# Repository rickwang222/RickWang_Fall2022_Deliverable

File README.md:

# RickWang_Fall2022_Deliverable

## 3D_Tag_Model Foler
3D_Holder.f3d file contains the 3D model of the 3D tag holder and can be opened and edited with Fusion 360
The PDF file contains the initial test result for 3 antennas and the materials used to build the 3D tag holder

## Arduino_Hat_RevB
This folder contains the original PCB file for the Arduino hat and can be open using Eagle, a BOM is also included in the form of Excel file

## PCB
This folder contains the Extension board PCB design as a Altium project. Download the entire folder and open the project will open both the PCB and schematic. The board is currently design to support 5 sets of antennas at the same time but can be expended by adding more ports. The input of the extension board is the output of the original Arduino hat. No softawre change needed for the extension board.

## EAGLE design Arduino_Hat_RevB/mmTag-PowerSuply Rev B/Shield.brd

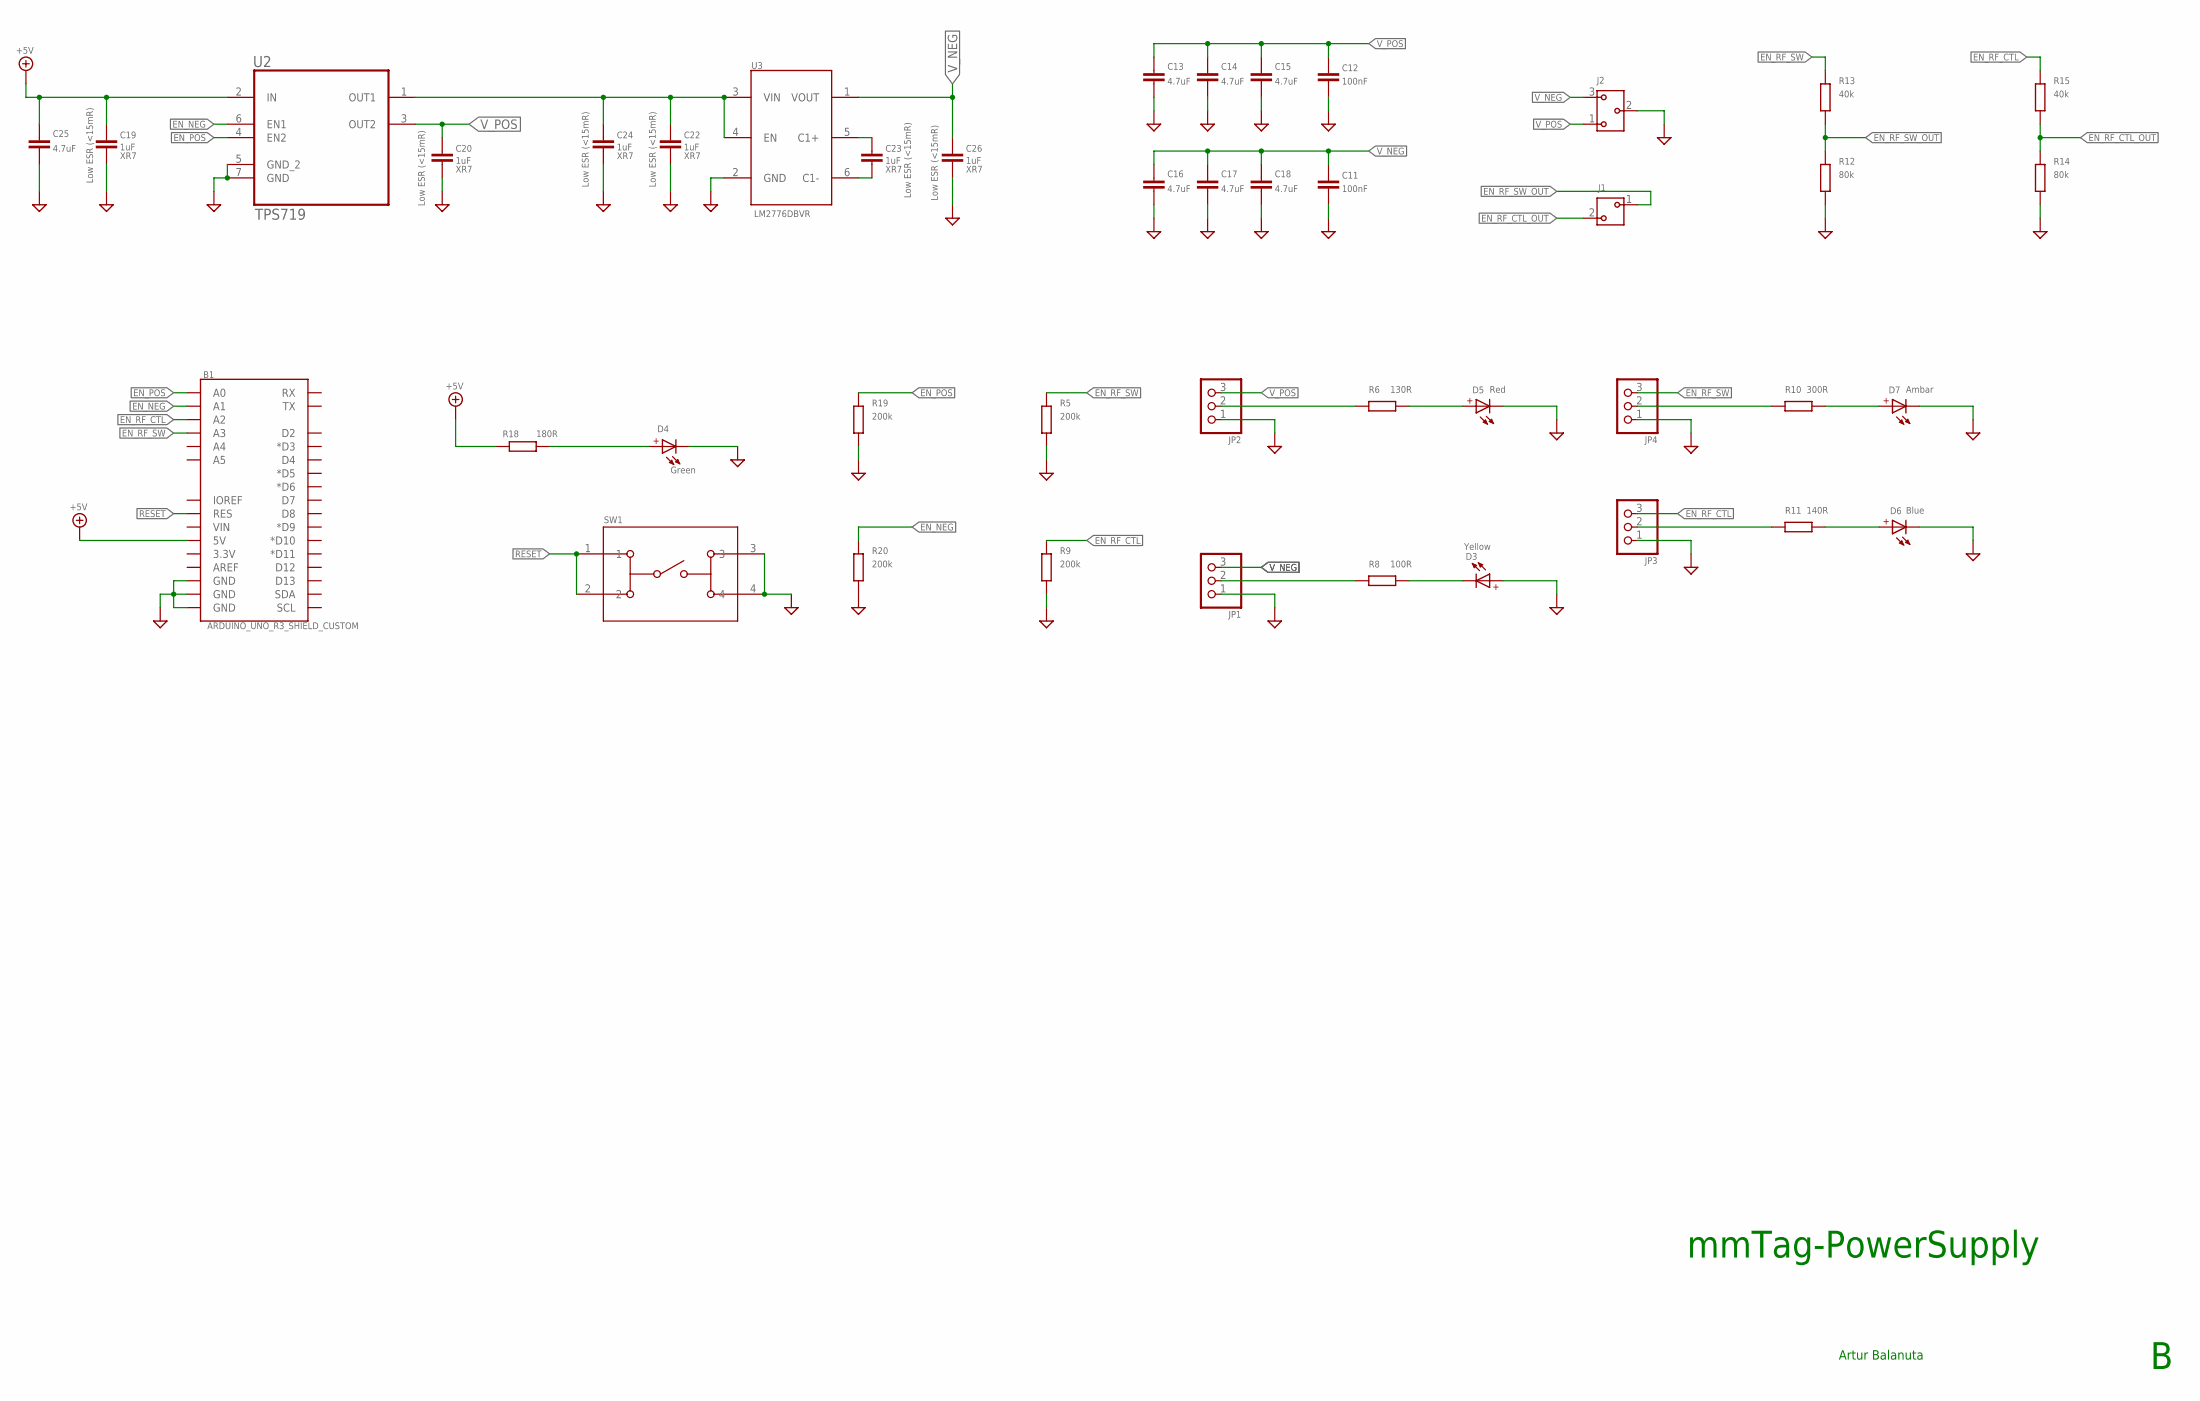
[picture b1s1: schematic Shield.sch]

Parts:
B1: ARDUINO_UNO_R3_SHIELD_CUSTOM; UNO_R3_SHIELD_NO_PROG
C11, C12: 100nF; C0603
C13, C14, C15, C16, C17, C18, C25: 4.7uF; C1206
C19, C20, C22, C23, C24, C26: 1uF; C0603
D3: WL-SMCW-150080YS75000; WL-SMCW_0805
D4: WL-SMCW-150080GS75000; WL-SMCW_0805
D5: WL-SMCW-150080RS75000; WL-SMCW_0805
D6: WL-SMCW-150080BS75000; WL-SMCW_0805
D7: WL-SMCW_150080AS75000; WL-SMCW_0805
J1: 691412320002
J2: 691412320003
JP1, JP2, JP3, JP4: PINHD-1X3; 1X03
R5, R9, R19, R20: 200k; R0603
R6: 130R; R0603
R8: 100R; R0603
R10: 300R; R0603
R11: 140R; R0603
R12, R14: 80k; R0603
R13, R15: 40k; R0603
R18: 180R; R0603
SW1: 1825910-6; SW4_1825910-B
U2: TPS719; SON6_5P200X200X80-7N
U3: LM2776DBVR; TEXAS_SOT23-6

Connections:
+5V: B1.5V, C19.1, C25.1, R18.1, U2.2 (IN)
EN_NEG: B1.A1, R20.1, U2.6 (EN1)
EN_POS: B1.A0, R19.1, U2.4 (EN2)
EN_RF_CTL: B1.A2, JP3.3, R9.1, R15.1
EN_RF_CTL_OUT: J1.2, R14.1, R15.2
EN_RF_SW: B1.A3, JP4.3, R5.1, R13.1
EN_RF_SW_OUT: J1.1, R12.1, R13.2
GND: B1.GND@0 (GND), B1.GND@1 (GND), B1.GND@2 (GND), C11.2, C12.2, C13.2, C14.2, C15.2, C16.2, C17.2, C18.2, C19.2, C20.2, C22.2, C24.2, C25.2, C26.2, D3.2 (+), D4.1 (-), D5.1 (-), D6.1 (-), D7.1 (-), J2.2, JP1.1, JP2.1, JP3.1, JP4.1, R5.2, R9.2, R12.2, R14.2, R19.2, R20.2, SW1.3, SW1.4, U2.5 (GND_2), U2.7 (GND), U3.2 (GND)
unnamed: D4.2 (+), R18.2
unnamed: C22.1, C24.1, U2.1 (OUT1), U3.3 (VIN), U3.4 (EN)
unnamed: C23.1, U3.5 (C1+)
unnamed: C23.2, U3.6 (C1-)
unnamed: D5.2 (+), R6.1
unnamed: D3.1 (-), R8.1
unnamed: JP2.2, R6.2
unnamed: JP1.2, R8.2
unnamed: D7.2 (+), R10.1
unnamed: D6.2 (+), R11.1
unnamed: JP4.2, R10.2
unnamed: JP3.2, R11.2
RESET: B1.RES, SW1.1, SW1.2
V_NEG: C11.1, C16.1, C17.1, C18.1, C26.1, J2.3, JP1.3, U3.1 (VOUT)
V_POS: C12.1, C13.1, C14.1, C15.1, C20.1, J2.1, JP2.3, U2.3 (OUT2)

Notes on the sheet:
mmTag-PowerSupply
Artur Balanuta

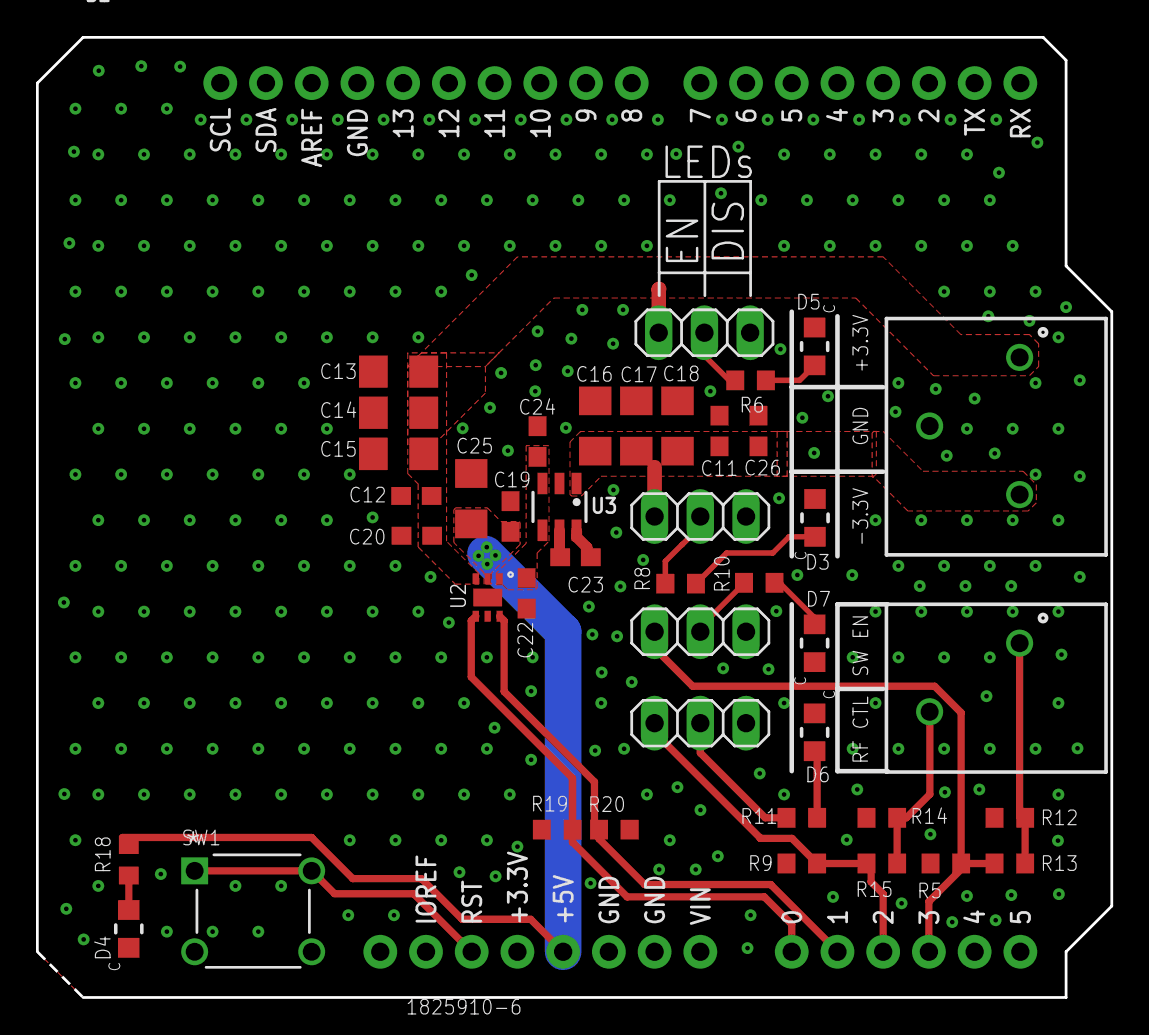
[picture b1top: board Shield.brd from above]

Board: 2 copper layers, 59.7 x 53.3 mm, 43 parts (0 on the bottom side), 23 nets.

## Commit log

2022-12-13 Create txt
2022-12-13 Create Chipless_Tag_Paper_Review
2022-12-13 Create t
2022-12-15 Create s

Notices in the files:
parts and their libraries:
Wurth_Elektronik_Optoelectronics_rev19b: Copyright: Würth Elektronik
COPYRIGHT: Copyright (C) 2016 Accelerated Designs. All rights reserved
